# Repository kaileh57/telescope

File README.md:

# DIY Newtonian Reflector Telescope

I designed my own telescope!

This is a pretty simple Newtonian Reflector style telescope, with a 114mm primary mirror, and a 25mm secondary mirror. I'm making it because I really love taking pictures of the stars, and was able to do some cool stuff a few weeks ago with a telescope at a family member's house! Hopefully this is a (comparatively) low cost way of getting into the field. There's a couple of great dark sky spots near me (Seattle), and hopefully I can update with some awesome pictures.

Hopefully, I can get some pretty cool images of galaxies and other cool objects, and I've included a barlow lens which should help with planetary photography.

I designed as much as possible myself! Unfortunately I don't have the capabilities to make motors or precision optics, and I'm using a modified version of the Crayford Focuser, as I'm not experienced enough with precision optics.

Crayford focuser: https://www.printables.com/model/125438-125-crayford-focuser-for-telescopes/files

## Assembly

PCB:

CAD:

Annotated CAD:

Azimuth and Altitude motors are connected to the PCB box via pre crimped cables, the Altitude cable should have a significant amount of lose cabling in order to accomodate the rotation of the base. 
The Raspberry PI HQ Camera is mounted to the end of the focuser, and should be attached via ribbon cable to the Raspberry PI Zero 2 W in the electronics enclosure, which is connected to the power management PCB. 
The GPS module should be plugged in to its header on the PCB, and should be placed in a location where it has a good view of the sky, for my configuration, it will be mounted on the side of a truck, and therefor is not practical to include in the CAD model. 
12v DC power comes in to the PCB from the side. 

Approximate limit switch positions, the model here is similar but not identical to the model I already have and am planning to install. The limit switches are wired into the appropriate port on the PCB and are used in calibration so that the telescope knows where its facing. 

Annotated Diagram:

**Telescope Focuser**: The 1.25" Crayford focuser design is from [aeberbach on Printables](https://www.printables.com/model/118575-125-crayford-focuser-for-telescopes), licensed under CC BY-NC 4.0.

## License

### Modified MIT License

```
MIT License (with exception)
Copyright (c) 2026 Kellen Heraty

Permission is hereby granted, free of charge, to any person obtaining a copy
of this software and associated documentation files (the "Software"), to deal
in the Software without restriction, including without limitation the rights
to use, copy, modify, merge, publish, distribute, sublicense, and/or sell
copies of the Software, and to permit persons to whom the Software is
furnished to do so, subject to the following conditions:

The above copyright notice and this permission notice shall be included in all
copies or substantial portions of the Software.

EXCEPTION: This license does NOT apply to the 1.25" Crayford focuser design 
files (STL and STEP files in the /focuser directory), which are provided by 
aeberbach under Creative Commons Attribution-NonCommercial 4.0 International 
License (CC BY-NC 4.0). Those files may not be used for commercial purposes.

THE SOFTWARE IS PROVIDED "AS IS", WITHOUT WARRANTY OF ANY KIND, EXPRESS OR
IMPLIED, INCLUDING BUT NOT LIMITED TO THE WARRANTIES OF MERCHANTABILITY,
FITNESS FOR A PARTICULAR PURPOSE AND NONINFRINGEMENT. IN NO EVENT SHALL THE
AUTHORS OR COPYRIGHT HOLDERS BE LIABLE FOR ANY CLAIM, DAMAGES OR OTHER
LIABILITY, WHETHER IN AN ACTION OF CONTRACT, TORT OR OTHERWISE, ARISING FROM,
OUT OF OR IN CONNECTION WITH THE SOFTWARE OR THE USE OR OTHER DEALINGS IN THE
SOFTWARE.
```

## Bill of Materials

### Optics & Camera System

| Category | Item | Qty | Specification | Source | Est. Cost | Link |
|----------|------|-----|---------------|--------|-----------|------|
| Optics | Primary Mirror (spherical) | 1 | 114mm diameter, f/8 (912mm FL), enhanced aluminum coating, BK7 glass, 14mm thick | AliExpress | $25.20 | [Link](https://www.aliexpress.us/item/3256802406856110.html) |
| Optics | Secondary Mirror (flat diagonal) | 1 | 25 minor axis, flat, enhanced aluminum coating | AliExpress | Included | Bundled with primary mirror set |
| Camera | Pi HQ Camera | 1 | Sony IMX477, 12.3MP, C-mount thread | Digikey | $50.00 | [Link](https://www.pishop.us/product/raspberry-pi-hq-camera-cs/?src=raspberrypi) |
| Camera | CSI cable (adapter) | 1 | 500mm length, 22-pin (0.5mm pitch) to 15-pin (1.0mm pitch) | AliExpress | $4.55 | [Link](https://www.aliexpress.us/item/3256808091724799.html) |
| Camera | C-mount to 1.25" adapter | 1 | Short profile, screws onto C-mount, 1.25" barrel slides into focuser | AliExpress | $2.84 | [Link](https://www.aliexpress.us/item/3256803470616922.html) |
| Accessory | 2x Barlow lens with T-ring | 1 | 1.25" barrel, 2x magnification, M42×0.75 T-thread for DSLR | AliExpress | $10.85 | [Link](https://www.aliexpress.us/item/3256802185717221.html) |

### OTA Tube Assembly & Mirror Cell

| Category | Item | Qty | Specification | Source | Est. Cost | Link |
|----------|------|-----|---------------|--------|-----------|------|
| OTA Hardware | Alignment dowel pins | 9 | M3×10mm steel, precision | Hardware Store | $4.00 | M3x10 dowel pins |
| OTA Hardware | Interior flocking material | 1 | Self-adhesive black velvet or flocking paper, ~900×450mm | AliExpress | $8.86 | [Link](https://www.aliexpress.us/item/3256807322733280.html) |
| Mirror Cell | Collimation bolts | 3 | M4×50mm hex head | Hardware Store | $5.00 | M4x50mm hex bolts |
| Mirror Cell | Compression springs | 3 | 0.5mm wire, 5mm od, 10mm long | Hardware Store | $4.00 | Between floor and floating plate for push-pull collimation |
| Mirror Cell | Flat washers (M4) | 6 | M4 size | Hardware Store | $2.00 | Top and bottom of each spring M4x9x0.5 |
| Mirror Cell | Wing nuts | 3 | M4 thread | Hardware Store | $3.50 | Hand-adjustable collimation from below |
| Mirror Cell | Cell mounting screws | 6 | M3×16mm socket head | Hardware Store | $4.50 | Attach cell housing to Segment 1 |
| Mirror Cell | Heat-set inserts (M3) | 6 | M3×6mm×5mm | Hardware Store | $6.00 | Press into Segment 1 for cell mounting |
| Mirror Cell | RTV Silicone | 1 | Sealant | AliExpress | $2.96 | [Link](https://www.aliexpress.us/item/3256807120493463.html) |
| Mirror Cell | Epoxy or super glue | 1 | Small tube | AliExpress | $2.31 | [Link](https://www.aliexpress.us/item/3256809235639574.html) |

### Secondary Spider Assembly

| Category | Item | Qty | Specification | Source | Est. Cost | Link |
|----------|------|-----|---------------|--------|-----------|------|
| Spider | Spider mounting screws | 4 | M3×16mm socket head | - | Included above | Mount spider ring to Segment 4 (through tube wall at 45° offsets) |
| Spider | Spider mounting nuts | 4 | M3 hex nuts | Hardware Store | $2.00 | M3 hex nuts for spider mounting |
| Spider | Secondary mirror adhesive | 1 | RTV silicone | - | Included above | Bonds secondary to 45° holder surface |

### Mount Structure

| Category | Item | Qty | Specification | Source | Est. Cost | Link |
|----------|------|-----|---------------|--------|-----------|------|
| Mount | Tube ring clamp bolts | 2 | M5×50mm hex head | Hardware Store | $4.00 | Clamp tube rings around OTA m5x50 |
| Mount | Tube ring to cradle bolts | 4 | M5×50mm hex head | - | Included above | Attach rings to altitude cradle |
| Mount | Fork to turntable bolts | 4 | M5×25mm socket head | Hardware Store | $3.50 | Secure forks to turntable |
| Mount | M5 nuts | 6 | Standard hex nuts | Hardware Store | $2.50 | For clamp and cradle bolts |
| Mount | M5 washers | 16 | Flat washers | Hardware Store | $3.00 | Under bolt heads and nuts |
| Mount | Heat-set inserts (M5) | 4 | M5 size | Hardware Store | $6.00 | In turntable for fork mounting |
| Mount | Hex nut (1/4-20) | 1 | 1/4-20 UNC thread | Hardware Store | $1.50 | Tripod mount in base center |
| Mount | Felt/foam tape | 1 | Self-adhesive, ~25mm wide roll | AliExpress | $2.24 | [Link](https://www.aliexpress.us/item/3256807381928957.html) |
| Mount | Lazy susan mounting screws | 8 | M4×12mm | Hardware Store | $4.00 | 4 per ring of lazy susan bearing |
| Mount | M4 nuts | 4 | Standard hex nuts | Hardware Store | $2.00 | Inner ring of lazy susan (through-hole to base) |

### Bearings

| Category | Item | Qty | Specification | Source | Est. Cost | Link |
|----------|------|-----|---------------|--------|-----------|------|
| Bearing | 608ZZ bearing | 1 | 8mm ID × 22mm OD × 7mm thick | AliExpress | $4.23 | [Link](https://www.aliexpress.us/item/3256805135171835.html) |
| Bearing | Lazy Susan bearing (Profile B) | 1 | 120mm OD, 79mm ID, 8.5mm thick, aluminum, PCD: 91.8mm inner / 109mm outer | AliExpress | $6.69 | [Link](https://www.aliexpress.us/item/3256807353712714.) |

### Drive Systems

| Category | Item | Qty | Specification | Source | Est. Cost | Link |
|----------|------|-----|---------------|--------|-----------|------|
| Alt Drive | NEMA17 Worm Gear Motor (1:32) | 1 | RobotDigg, 42×42×48mm motor + 40×58×27mm gearbox, 8mm D-shaft output, 1.8Nm torque, 1.7A | AliExpress | $28.06 | [Link](https://www.aliexpress.us/item/3256808139356937.html) |
| Alt Drive | Shaft coupler (8mm-8mm) | 1 | Aluminum, ~25mm body length | AliExpress | $3.49 | [Link](https://www.aliexpress.us/item/3256805451220598.html) |
| Alt Drive | Motor mount screws | 4 | M4×10mm flat head | Hardware Store | $3.00 | - |
| Alt Drive | Mount plate screws | 4 | M4×20mm socket head | Hardware Store | $3.50 | Attach motor mount plate to left fork |
| Az Drive | NEMA17 Worm Gear Motor (1:32) | 1 | RobotDigg, same spec as altitude motor | AliExpress | $28.06 | [Link](https://www.aliexpress.us/item/3256808139356937.html) |
| Az Drive | GT2 timing belt (6mm) | 1 | ~800mm length, open-ended, cut to fit | AliExpress | $8.48 | [Link](https://www.aliexpress.us/item/3256802121511505.html) |
| Az Drive | GT2 pulley (30T) | 1 | 30 teeth, 8mm bore, 6mm belt width | AliExpress | $3.65 | [Link](https://www.aliexpress.us/item/3256805593092055.html) |
| Az Drive | Motor mount screws | 4 | M4×12mm flat head | - | Included above | Through slotted holes in base extension tab |

### PCB Through-Hole Components

| Category | Item | Qty | Specification | Source | Est. Cost | Link |
|----------|------|-----|---------------|--------|-----------|------|
| PCB TH | 100µF 25V electrolytic capacitor | 3 | Through-hole, radial | AliExpress | $2.32 | [Link](https://www.aliexpress.us/item/3256805247425905.html) |
| PCB TH | 220µF 10V electrolytic capacitor | 1 | Through-hole, radial | AliExpress | $2.15 | [Link](https://www.aliexpress.us/item/3256805247425905.html) |
| PCB TH | 2×20 female header | 1 | 2.54mm pitch, through-hole | AliExpress | $1.42 | [Link](https://www.aliexpress.us/item/2251832667900858.html) |
| PCB TH | 1×8 female header | 4 | 2.54mm pitch, through-hole | AliExpress | $1.61 | [Link](https://www.aliexpress.us/item/2255801012106911.html) |
| PCB TH | JST-XH 4-pin connector | 2 | Vertical | - | Included with pigtails kit | Motor output connectors (J_MOT1, J_MOT2) |
| PCB TH | DC barrel jack | 1 | 5.5×2.1mm, center positive | Digikey | $0.64 | [Link](https://www.digikey.com/en/products/detail/same-sky-formerly-cui-devices/PJ-002AH/408446) |

### Electronics Modules

| Category | Item | Qty | Specification | Source | Est. Cost | Link |
|----------|------|-----|---------------|--------|-----------|------|
| Module | Raspberry Pi Zero 2 W | 1 | PI zero 2 w | Digikey | $15.00 | [Link](https://www.digikey.com/en/products/detail/raspberry-pi/SC1176/15298147) |
| Module | TMC2209 StepStick | 2 | BIGTREETECH V1.2 or V1.3 | AliExpress | $9.72 | [Link](https://www.aliexpress.us/item/2255800257311131.html) |
| Module | NEO-6M GPS module | 1 | 3.3V logic output ONLY - 5V will damage Pi! | AliExpress | $8.90 | [Link](https://www.aliexpress.us/item/3256808037885086.html) |
| Module | MP1584 buck converter module | 1 | Adjustable output, set to 5.0-5.1V, needs to be adjustable for precision | AliExpress | $1.57 | [Link](https://www.aliexpress.us/item/3256808313082613.html) |
| Wiring | 22awg wire | 20cm | For connecting MP1584, hard to find in small quantities | AliExpress | $3.04 | [Link](https://www.aliexpress.us/item/3256808757002563.html) |
| Module | 10×10mm heatsinks | 4 | Aluminum, with thermal adhesive tape | AliExpress | $3.94 | [Link](https://www.aliexpress.us/item/3256804749177306.html) |

### Power & Wiring

| Category | Item | Qty | Specification | Source | Est. Cost | Link |
|----------|------|-----|---------------|--------|-----------|------|
| Power | 12V 5A DC power supply | 1 | 5.5×2.1mm barrel jack output, center positive | AliExpress | $17.22 | [Link](https://www.aliexpress.us/item/3256807351095066.html) |
| Wiring | JST-XH 4-pin pigtails | 4 | Pre-crimped leads, ~30cm | AliExpress | $7.13 | [Link](https://www.aliexpress.us/item/3256808528022826.html) |
| Wiring | Heat shrink tubing | 1 | Assorted sizes kit | - | Included | Insulate splices |
| Wiring | Motor cables | 2 | 4-wire, ~50cm, usually included with motors | With motors | Included | Check if included with RobotDigg motors |
| Wiring | Motor extension | 2 | Allows the cables to reach | AliExpress | $6.05 | [Link](https://www.aliexpress.us/item/3256807018820517.html) |

### Accessories

| Category | Item | Qty | Specification | Source | Est. Cost | Link |
|----------|------|-----|---------------|--------|-----------|------|
| Accessory | Rubber friction pads | 4 | Self-adhesive | AliExpress | $2.18 | [Link](https://www.aliexpress.us/item/3256806771014461.html) |

### Focuser Components

| Category | Item | Qty | Specification | Source | Est. Cost | Link |
|----------|------|-----|---------------|--------|-----------|------|
| Motion | MR83ZZ bearings | 4 | 3mm ID × 8mm OD × 3mm thick | AliExpress | $5.24 | [Link](https://www.aliexpress.us/item/3256804648772069.html) |
| Motion | Steel shaft | 1 | 5mm diameter × 90mm length, stainless | AliExpress | $2.31 | [Link](https://www.aliexpress.us/item/3256805290944526.html) |
| Motion | Aluminum flat bar | 1 | 10mm × 3mm × 150mm (cut 64+64+37 = 165mm needed) | AliExpress | $3.52 | [Link](https://www.aliexpress.us/item/3256805124428430.html) |
| Motion | Compression springs | 2 | OD < 5mm, ~6.5mm length, STIFF (not pen springs) | Hardware Store | $3.00 | Small compression springs |
| Inserts | M3 heat-set inserts | 8 | M3 × 5mm L × 4.5mm OD | Hardware Store | $8.00 | M3 heat-set inserts |
| Inserts | M4 heat-set inserts | 4 | M4 × 6mm L × 5.5mm OD | Hardware Store | $6.00 | M4 heat-set inserts |
| Bolts | M3×10mm button head | 4 | Button head, bearing axles | Hardware Store | $3.00 | Button head screws for bearing axles |
| Bolts | M3×12mm socket head | 4 | Socket head, drawtube cap | Hardware Store | $3.00 | Socket head for drawtube cap |
| Bolts | M3×20mm socket head | 4 | Socket head, front cap to base | Hardware Store | $3.50 | Socket head for front cap |
| Bolts | M4×12mm socket head | 4 | Socket head, mount focuser to telescope | - | Included above | - |
| Nuts | M3 nylock nuts | 4 | Nylon insert lock nuts, secure bearing axles | Hardware Store | $2.50 | Nylock nuts for bearing security |
| Nuts | M3 hex nut | 1 | Standard, pressed into front cap for tension screw | - | Included above | - |
| Nuts | M3 thumbscrew | 1 | Knurled head, main tension adjustment | Hardware Store | $3.00 | Knurled thumbscrew for tension |
| Nuts | M3 set screws | 2 | Grub screws | Hardware Store | $2.00 | - |

### 3D Printed Components

Hoping to print all from the same person, near me in Seattle. Mostly PETG, some PLA, TPU would be cool but not needed at all.

| Component | Material | Infill | Est. Print Time | Notes |
|-----------|----------|--------|-----------------|-------|
| **OTA - Tube Assembly** |
| Tube_Segment_1 (rear) | PETG | 30% gyroid | ~12 hours | Mirror cell interface, 220mm length, 130mm ID, 4mm wall |
| Tube_Segment_2 | PETG | 30% gyroid | ~12 hours | Middle segment, alignment pins at joints |
| Tube_Segment_3 | PETG | 30% gyroid | ~12 hours | Middle segment |
| Tube_Segment_4 (front) | PETG | 30% gyroid | ~12 hours | Focuser boss (70×70mm), spider mount holes at 45° offset |
| **OTA - Mirror Cell (Hadley-style)** |
| Primary_Mirror_Cell_Housing | PETG | 30% | ~8 hours | 154mm OD flange, 120mm ID wall, floor with 40mm vent, 3× spring bosses |
| Floating_Plate | PETG | 30% | ~2 hours | 118mm OD × 8mm, hex pockets for bolt capture, 115mm mirror recess |
| **OTA - Secondary Assembly** |
| Secondary_Spider | PLA or PETG | 40% | ~4 hours | 4-vane design, ring fits inside tube top, 45° mirror holder, 3× collimation screws |
| **OTA - Focuser (aeberbach Crayford - Printables #125438)** |
| Focuser_Body | PETG | 40% | ~2.5 hours | Main body with 4× bearing mounts, 4× M3 insert holes for front cap |
| Pinion_Block | PETG | 40% | ~30 min | Shaft passes through; 2× spring holes in back for tension |
| Front_Cap | PETG | 40% | ~45 min | Recess for M3 hex nut (tension screw); mounts with 4× M3×20mm |
| Drawtube | PETG | 30% | ~1.5 hours | Print flange-down; slots for 2× 64mm aluminum strips |
| Drawtube_Cap | PETG | 30% | ~30 min | Print flange-down; secures aluminum strips; 4× M3×12mm + M3 inserts |
| Pinion_Spacer (×2) | PETG | 30% | ~15 min total | Covers exposed shaft ends outside body |
| Focus_Knob (×2) | PETG | 30% | ~30 min total | Small knob(s) |
| **OTA - Dust Covers** |
| Front_Dust_Cap | PLA or PETG | 20% | ~1 hour | 139mm ID, 145mm OD, 15mm tall with pull tab |
| Rear_Dust_Cover | PLA or PETG | 20% | ~1 hour | 160mm OD disc with 154/148mm retention ring |
| Focuser_Cap | PLA | 20% | ~15 min | 31.5mm plug, 38mm flange, friction fit |
| **Mount - Tube Rings & Cradle** |
| Tube_Ring (×2) | PETG | 30% | ~4 hours total | 148mm OD, 140mm ID, split clamp, mounting boss for cradle |
| Altitude_Cradle | PETG | 30% | ~3 hours | 200×80×8mm plate, LEFT shaft 45mm (motor side), RIGHT shaft 25mm |
| **Mount - Forks** |
| Altitude_Fork_LEFT | PETG | 30% | ~8 hours | 60×120×15mm, 4× M4 heat-set holes for motor mount plate |
| Altitude_Fork_RIGHT | PETG | 30% | ~8 hours | 60×120×15mm, 608ZZ bearing pocket for pivot |
| Alt_Motor_Mount_Plate | PETG | 30% | ~1 hour | 60×60×5mm, NEMA17 pattern, 25mm center clearance hole |
| **Mount - Azimuth Base** |
| Azimuth_Stationary_Base | PETG | 25% | ~12 hours | 280mm dia + motor extension tab (80×70×8mm), tripod mount, lazy susan PCD 91.8mm |
| Azimuth_Turntable | PETG | 25% | ~6 hours | 220mm OD, 80mm center hole, lazy susan PCD 109mm, fork mounting bosses |
| Base_Feet (×4) | PETG or TPU | 30% | ~2 hours | ~40mm tall for gearbox clearance, rubber pad attachment |
| **Electronics** |
| Electronics_Enclosure | PLA | 20% | ~6 hours | Box for PCB + Pi Zero, ventilation slots, friction-fit lid |

### PCB SMT Components (JLCPCB Assembly)

| Designator | Value/Part | LCSC# | Qty/Board | Ext (2 boards) | Notes |
|------------|------------|--------|-----------|----------------|-------|
| C3 | 22uF 16V Tantalum | C782264 | 1 | $0.67 | Extended |
| C4,C7,C8,C9,C10,C11 | 100nF 0603 | C14663 | 6 | $0.17 | Basic (6× ~$0.03) |
| D1 | 6.8V Zener SOD-123 | C2120 | 1 | $0.26 | Extended |
| F1 | 4A Polyfuse 2920 | C139284 | 1 | $0.61 | Littelfuse Extended |
| F2 | 1.5A Polyfuse 1206 | C70083 | 1 | $0.33 | TECHFUSE Extended |
| Q1 | AO3401A P-FET | C15127 | 1 | $0.11 | Basic |
| R1,R2,R3 | 10k 0603 | C25804 | 3 | $0.02 | Basic |
| U1 | AMS1117-3.3 | C6186 | 1 | $0.32 | Basic |

**SMT Total: $2.49** (from JLCPCB quote)

### Cost Summary

| Source | Total |
|--------|-------|
| Digikey | $72.69 |
| AliExpress | $285.26 |
| Hardware Store | I will pay/find these parts |
| JLCPCB | $45.71 |
| **Total** | **$403.66** |

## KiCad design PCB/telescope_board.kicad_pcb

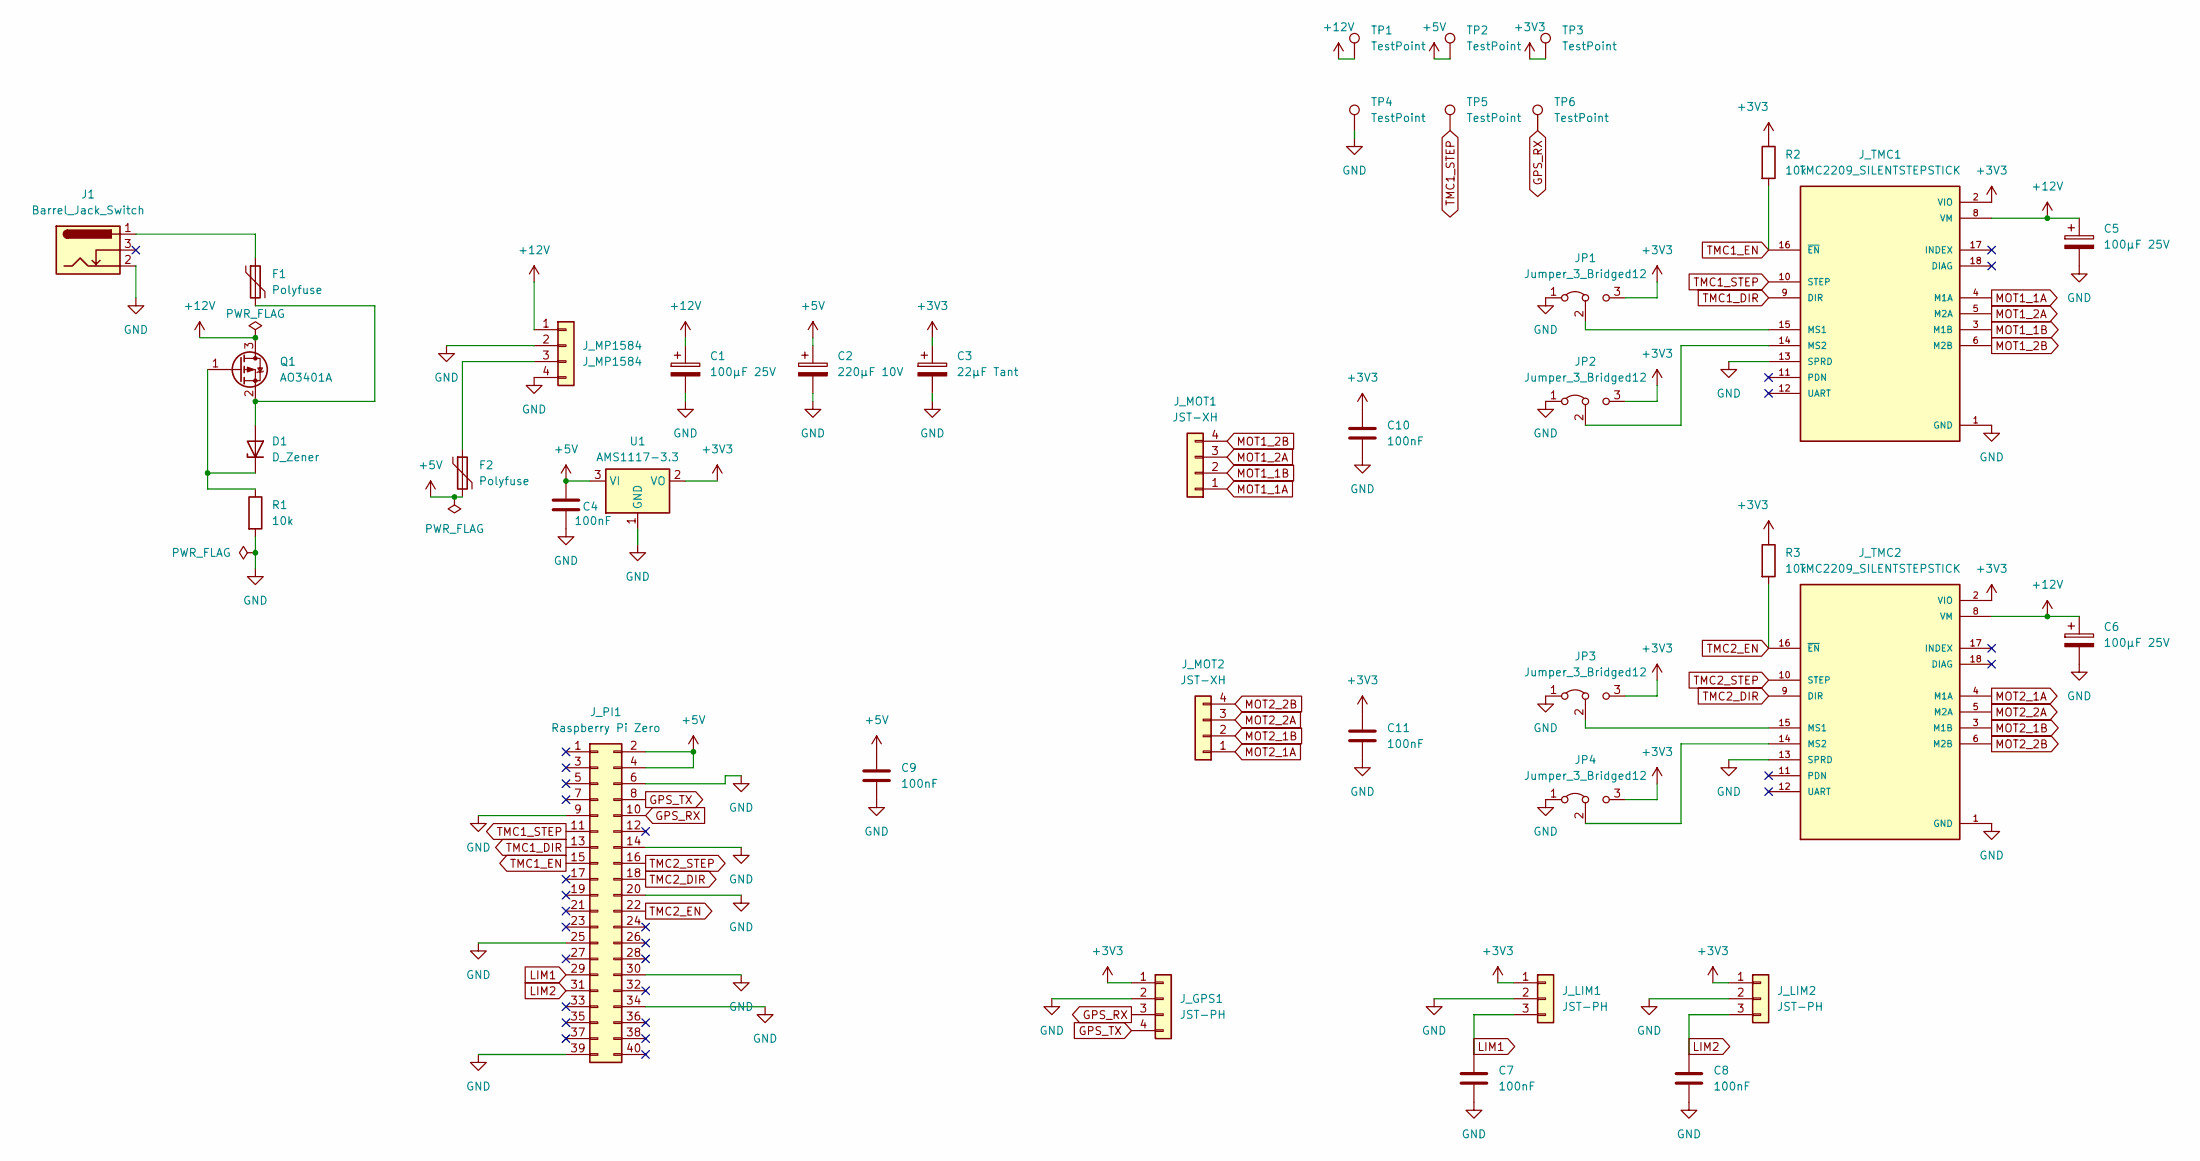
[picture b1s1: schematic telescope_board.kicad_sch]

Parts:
C1, C5, C6: 100µF 25V; CP_Radial_D6.3mm_P2.50mm
C2: 220µF 10V; CP_Radial_D8.0mm_P3.50mm
C3: 22µF Tant; CP_EIA-3216-18_Kemet-A
C4, C7, C8, C9, C10, C11: 100nF; C_0603_1608Metric
D1: D_Zener; D_SOD-123
F1: Polyfuse; Fuse_2920_7451Metric
F2: Polyfuse; Fuse_1206_3216Metric
J1: Barrel_Jack_Switch; BarrelJack_Horizontal
JP1, JP2, JP3, JP4: Jumper_3_Bridged12; SolderJumper-3_P1.3mm_Bridged12_RoundedPad1.0x1.5mm
J_GPS1: JST-PH; JST_PH_B4B-PH-K_1x04_P2.00mm_Vertical
J_LIM1, J_LIM2: JST-PH; JST_PH_B3B-PH-K_1x03_P2.00mm_Vertical
J_MOT1, J_MOT2: JST-XH; JST_XH_B4B-XH-A_1x04_P2.50mm_Vertical
J_MP1584: J_MP1584; PinHeader_1x04_P2.54mm_Vertical
J_PI1: Raspberry Pi Zero; PinSocket_2x20_P2.54mm_Vertical
J_TMC1, J_TMC2: TMC2209_SILENTSTEPSTICK; MODULE_TMC2209_SILENTSTEPSTICK; PARTREV 1.20
Q1: AO3401A; SOT-23
R1, R2, R3: 10k; R_0603_1608Metric
TP1, TP2, TP3, TP4, TP5, TP6: TestPoint; TestPoint_Pad_D1.5mm
U1: AMS1117-3.3; SOT-223-3_TabPin2

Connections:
+3V3: C3.1, C10.1, C11.1, JP1.3 (B), JP2.3 (B), JP3.3 (B), JP4.3 (B), J_GPS1.1, J_LIM1.1, J_LIM2.1, J_TMC1.2 (VIO), J_TMC2.2 (VIO), R2.1, R3.1, TP3.1, U1.2 (VO)
+5V: C2.1, C4.1, C9.1, F2.2, J_PI1.2, J_PI1.4, TP2.1, U1.3 (VI)
+12V: C1.1, C5.1, C6.1, J_MP1584.1, J_TMC1.8 (VM), J_TMC2.8 (VM), Q1.3 (D), TP1.1
GND: C1.2, C2.2, C3.2, C4.2, C5.2, C6.2, C7.2, C8.2, C9.2, C10.2, C11.2, J1.2, JP1.1 (A), JP2.1 (A), JP3.1 (A), JP4.1 (A), J_GPS1.2, J_LIM1.2, J_LIM2.2, J_MP1584.2, J_MP1584.4, J_PI1.6, J_PI1.9, J_PI1.14, J_PI1.20, J_PI1.25, J_PI1.30, J_PI1.34, J_PI1.39, J_TMC1.1 (GND), J_TMC1.7 (GND), J_TMC1.13 (SPRD), J_TMC2.1 (GND), J_TMC2.7 (GND), J_TMC2.13 (SPRD), R1.2, TP4.1, U1.1 (GND)
GPS_RX: J_GPS1.3, J_PI1.10, TP6.1
GPS_TX: J_GPS1.4, J_PI1.8
LIM1: C7.1, J_LIM1.3, J_PI1.29
LIM2: C8.1, J_LIM2.3, J_PI1.31
MOT1_1A: J_MOT1.1, J_TMC1.4 (M1A)
MOT1_1B: J_MOT1.2, J_TMC1.3 (M1B)
MOT1_2A: J_MOT1.3, J_TMC1.5 (M2A)
MOT1_2B: J_MOT1.4, J_TMC1.6 (M2B)
MOT2_1A: J_MOT2.1, J_TMC2.4 (M1A)
MOT2_1B: J_MOT2.2, J_TMC2.3 (M1B)
MOT2_2A: J_MOT2.3, J_TMC2.5 (M2A)
MOT2_2B: J_MOT2.4, J_TMC2.6 (M2B)
unnamed: D1.2 (A), F1.2, Q1.2 (S)
unnamed: D1.1 (K), Q1.1 (G), R1.1
unnamed: F1.1, J1.1
unnamed: JP1.2 (C), J_TMC1.15 (MS1)
unnamed: JP2.2 (C), J_TMC1.14 (MS2)
unnamed: JP3.2 (C), J_TMC2.15 (MS1)
unnamed: JP4.2 (C), J_TMC2.14 (MS2)
unnamed: F2.1, J_MP1584.3
TMC1_DIR: J_PI1.13, J_TMC1.9 (DIR)
TMC1_EN: J_PI1.15, J_TMC1.16 (~EN), R2.2
TMC1_STEP: J_PI1.11, J_TMC1.10 (STEP), TP5.1
TMC2_DIR: J_PI1.18, J_TMC2.9 (DIR)
TMC2_EN: J_PI1.22, J_TMC2.16 (~EN), R3.2
TMC2_STEP: J_PI1.16, J_TMC2.10 (STEP)

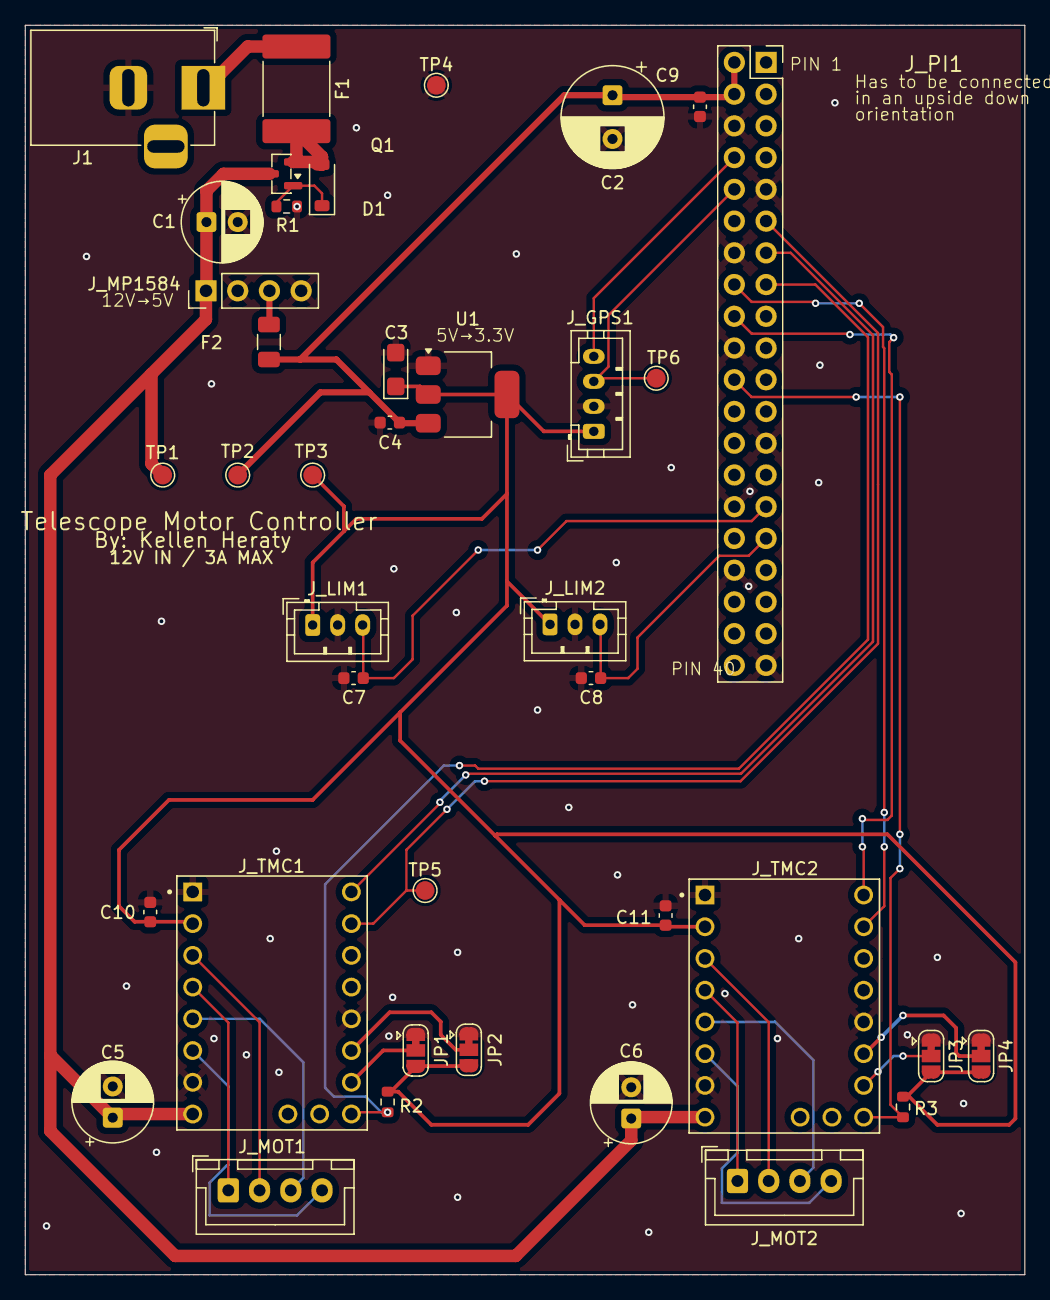
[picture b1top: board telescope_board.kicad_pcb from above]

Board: 2 copper layers, 80.0 x 100.0 mm, 39 parts (0 on the bottom side), 30 nets.

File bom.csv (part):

Category,Item,Qty,Specification,Source,Est. Cost (not incl Shipping or tax),Link/Notes,,
OPTICS,,,,,,,,
Optics,Primary Mirror (spherical),1,"114mm diameter, f/8 (912mm FL), enhanced aluminum coating, BK7 glass, 14mm thick",AliExpress,$25.20,"spherical is much cheaper than parabolic, but slightly worse https://www.aliexpress.us/item/3256802406856110.html",,
Optics,Secondary Mirror (flat diagonal),1,"25 minor axis, flat, enhanced aluminum coating",AliExpress,Included,Bundled with primary mirror set,,
CAMERA SYSTEM,,,,,,,,
Camera,Pi HQ Camera,1,"Sony IMX477, 12.3MP, C-mount thread",Digikey,$50.00,https://www.pishop.us/product/raspberry-pi-hq-camera-cs/?src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,,SC
Camera,CSI cable (adapter),1,"500mm length, 22-pin (0.5mm pitch) to 15-pin (1.0mm pitch)",AliExpress,$4.55,500mm version https://www.aliexpress.us/item/3256808091724799.html,,
Camera,"C-mount to 1.25"" adapter",1,"Short profile, screws onto C-mount, 1.25"" barrel slides into focuser",AliExpress,$2.84,https://www.aliexpress.us/item/3256803470616922.html?,,
OPTICAL ACCESSORIES,,,,,,,,
Accessory,2x Barlow lens with T-ring,1,"1.25"" barrel, 2x magnification, M42×0.75 T-thread for DSLR",AliExpress,$10.85,massively helps with planetary imaging https://www.aliexpress.us/item/3256802185717221.html,,
OTA TUBE ASSEMBLY,,,,,,,,
OTA Hardware,Alignment dowel pins,9,"M3×10mm steel, precision",Hardware Store,$4.00,m3x10 dowel pins,,
OTA Hardware,Interior flocking material,1,"Self-adhesive black velvet or flocking paper, ~900×450mm",AliExpress,$8.86,45cm x 10m https://www.aliexpress.us/item/3256807322733280.html,,
PRIMARY MIRROR CELL,,,,,,,,
Mirror Cell,Collimation bolts,3,M4×50mm hex head,Hardware Store,$5.00,m4x50mm hex bolts,,
Mirror Cell,Compression springs,3,"0.5mm wire, 5mm od, 10mm long",Hardware Store,$4.00,"Between floor and floating plate for push-pull collimation: 0.5mm wire, 5mm od, 10mm long",,
Mirror Cell,Flat washers (M4),6,M4 size,Hardware Store,$2.00,Top and bottom of each spring M4x9x0.5,,
Mirror Cell,Wing nuts,3,M4 thread,Hardware Store,$3.50,Hand-adjustable collimation from below,,
Mirror Cell,Cell mounting screws,6,M3×16mm socket head,Hardware Store,$4.50,Attach cell housing to Segment 1,,
Mirror Cell,Heat-set inserts (M3),6,M3×6mm×5mm,Hardware Store,$6.00,Press into Segment 1 for cell mounting,,
Mirror Cell,RTV Silicone,1,Sealant,AliExpress,$2.96,"Bonds mirror to floating plate; flexible for thermal expansion, https://www.aliexpress.us/item/3256807120493463.html",,
Mirror Cell,Epoxy or super glue,1,Small tube,AliExpress,$2.31,Permanently captures M4 bolt heads in hex pockets https://www.aliexpress.us/item/3256809235639574.html,,
SECONDARY SPIDER ASSEMBLY,,,,,,,,
Spider,Spider mounting screws,4,M3×16mm socket head,,Included above,Mount spider ring to Segment 4 (through tube wall at 45° offsets),,
Spider,Spider mounting nuts,4,M3 hex nuts,Hardware Store,$2.00,M3 hex nuts for spider mounting,,
Spider,Secondary mirror adhesive,1,RTV silicone,,Included above,Bonds secondary to 45° holder surface,,
MOUNT STRUCTURE,,,,,,,,
Mount,Tube ring clamp bolts,2,M5×50mm hex head,Hardware Store,$4.00,Clamp tube rings around OTA m5x50,,
Mount,Tube ring to cradle bolts,4,M5×50mm hex head,,Included above,Attach rings to altitude cradle,,
Mount,Fork to turntable bolts,4,M5×25mm socket head,Hardware Store,$3.50,Secure forks to turntable,,
Mount,M5 nuts,6,Standard hex nuts,Hardware Store,$2.50,For clamp and cradle bolts,,
Mount,M5 washers,16,Flat washers,Hardware Store,$3.00,Under bolt heads and nuts,,
Mount,Heat-set inserts (M5),4,M5 size,Hardware Store,$6.00,In turntable for fork mounting,,
Mount,Hex nut (1/4-20),1,1/4-20 UNC thread,Hardware Store,$1.50,Tripod mount in base center,,
Mount,Felt/foam tape,1,"Self-adhesive, ~25mm wide roll",AliExpress,$2.24,"Line inside of tube rings to protect OTA, general adhesive, 25mm https://www.aliexpress.us/item/3256807381928957.html",,
Mount,Lazy susan mounting screws,8,M4×12mm,Hardware Store,$4.00,4 per ring of lazy susan bearing,,
Mount,M4 nuts,4,Standard hex nuts,Hardware Store,$2.00,Inner ring of lazy susan (through-hole to base),,
BEARINGS,,,,,,,,
Bearing,608ZZ bearing,1,8mm ID × 22mm OD × 7mm thick,AliExpress,$4.23,"Altitude pivot (non-motor side, right fork), https://www.aliexpress.us/item/3256805135171835.html",,
Bearing,Lazy Susan bearing (Profile B),1,"120mm OD, 79mm ID, 8.5mm thick, aluminum, PCD: 91.8mm inner / 109mm outer",AliExpress,$6.69,Azimuth rotation; https://www.aliexpress.us/item/3256807353712714.,,
ALTITUDE DRIVE SYSTEM,,,,,,,,
Alt Drive,NEMA17 Worm Gear Motor (1:32),1,"RobotDigg, 42×42×48mm motor + 40×58×27mm gearbox, 8mm D-shaft output, 1.8Nm torque, 1.7A",robotdigg.com,$28.06,https://www.aliexpress.us/item/3256808139356937.html,,
Alt Drive,Shaft coupler (8mm-8mm),1,"Aluminum, ~25mm body length",AliExpress,$3.49,"Connects motor shaft to cradle pivot shaft, 8x8 https://www.aliexpress.us/item/3256805451220598.html",,
Alt Drive,Motor mount screws,4,M4×10mm flat head,Hardware Store,$3.00,,,
Alt Drive,Mount plate screws,4,M4×20mm socket head,Hardware Store,$3.50,Attach motor mount plate to left fork,,
AZIMUTH DRIVE SYSTEM,,,,,,,,
Az Drive,NEMA17 Worm Gear Motor (1:32),1,"RobotDigg, same spec as altitude motor",robotdigg.com,$28.06,https://www.aliexpress.us/item/3256808139356937.html,,
Az Drive,GT2 timing belt (6mm),1,"~800mm length, open-ended, cut to fit",AliExpress,$8.48,"Wraps around 220mm turntable edge (~690mm circumference), 1m, 6mm width, https://www.aliexpress.us/item/3256802121511505.html",,
Az Drive,GT2 pulley (30T),1,"30 teeth, 8mm bore, 6mm belt width",AliExpress,$3.65,"Mounts on shaft extension above motor, 30 teeth, 6mm, 8mm bore https://www.aliexpress.us/item/3256805593092055.html",,
Az Drive,Motor mount screws,4,"M4×12mm flat head, needs to be flat head for clearance",,Included above,Through slotted holes in base extension tab,,
PCB - THROUGH-HOLE COMPONENTS,,,,,,,,
PCB TH,100µF 25V electrolytic capacitor,3,"Through-hole, radial",AliExpress,$2.32,1× input bulk + 2× TMC2209 VMOT 25v100uf 6x11 https://www.aliexpress.us/item/3256805247425905.html,,
PCB TH,220µF 10V electrolytic capacitor,1,"Through-hole, radial",AliExpress,$2.15,"5V rail bulk near Pi header, 10v220uf 5x11 https://www.aliexpress.us/item/3256805247425905.html",,
PCB TH,2×20 female header,1,"2.54mm pitch, through-hole",AliExpress,$1.42,Pi Zero socket 1x20pin https://www.aliexpress.us/item/2251832667900858.html,,
PCB TH,1×8 female header,4,"2.54mm pitch, through-hole",AliExpress,$1.61,TMC2209 StepStick sockets 1x8pin https://www.aliexpress.us/item/2255801012106911.html,,
PCB TH,JST-XH 4-pin connector,2,vertical,,Included with pigtails kit,"Motor output connectors (J_MOT1, J_MOT2)",,
PCB TH,DC barrel jack,1,"5.5×2.1mm, center positive",Digikey,$0.64,MUST be from a reliable distributer as we need 12v 5a https://www.digikey.com/en/products/detail/same-sky-formerly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,,
ELECTRONICS - MODULES,,,,,,,,
Module,Raspberry Pi Zero 2 W,1,PI zero 2 w,Digikey,$15.00,"Main controller - camera, GPS, motor control, https://www.digikey.com/en/products/detail/raspberry-pi/SC11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",,
Module,TMC2209 StepStick,2,BIGTREETECH V1.2 or V1.3,AliExpress,$9.72,"Stepper drivers, 2A max, STEP/DIR mode https://www.aliexpress.us/item/2255800257311131.html",,
Module,NEO-6M GPS module,1,3.3V logic output ONLY - 5V will damage Pi!,AliExpress,$8.90,Position and time sync for GoTo https://www.aliexpress.us/item/3256808037885086.html,,
Module,MP1584 buck converter module,1,"Adjustable output, set to 5.0-5.1V, needs to be adjustable for precision",AliExpress,$1.57,12V to 5V for Pi Zero https://www.aliexpress.us/item/3256808313082613.html,,
Wiring,22awg wire,20cm,"For connecting MP1584, hard to find in small quantities",AliExpress,$3.04,22 awg https://www.aliexpress.us/item/3256808757002563.html,,
Module,10×10mm heatsinks,4,"Aluminum, with thermal adhesive tape",AliExpress,$3.94,1× MP1584 (mandatory!) + 1 for pi + 2× TMC2209 (in case they dont include it) https://www.aliexpress.us/item/3256804749177306.html,,
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
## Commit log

2025-12-25 the PCB
2026-01-01 pcb files
2026-01-01 source files and software
2026-01-01 quick spec update
2026-01-01 Add telescope project details and modified MIT license
    Added detailed description of telescope design and components, including images and license information.
2026-01-01 Add MIT License with exceptions for certain files
    Added the MIT License with an exception for specific files.
2026-01-01 added stl files for printing
2026-01-01 pcb prod files
2026-01-01 bom fix
2026-01-02 final
2026-01-02 minor adjust to focuser
2026-01-02 fixed a math error
2026-01-06 Enhance README with assembly images and diagrams
    Added images and diagrams for PCB, CAD, and annotated diagram in the assembly section.
2026-01-09 Enhance README with annotated CAD and component details
    Added annotated CAD details and images for components and connections.
2026-01-24 fix spider
